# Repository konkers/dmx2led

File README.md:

# dmx2led
DMX512 to Addressable RGB LED Converter

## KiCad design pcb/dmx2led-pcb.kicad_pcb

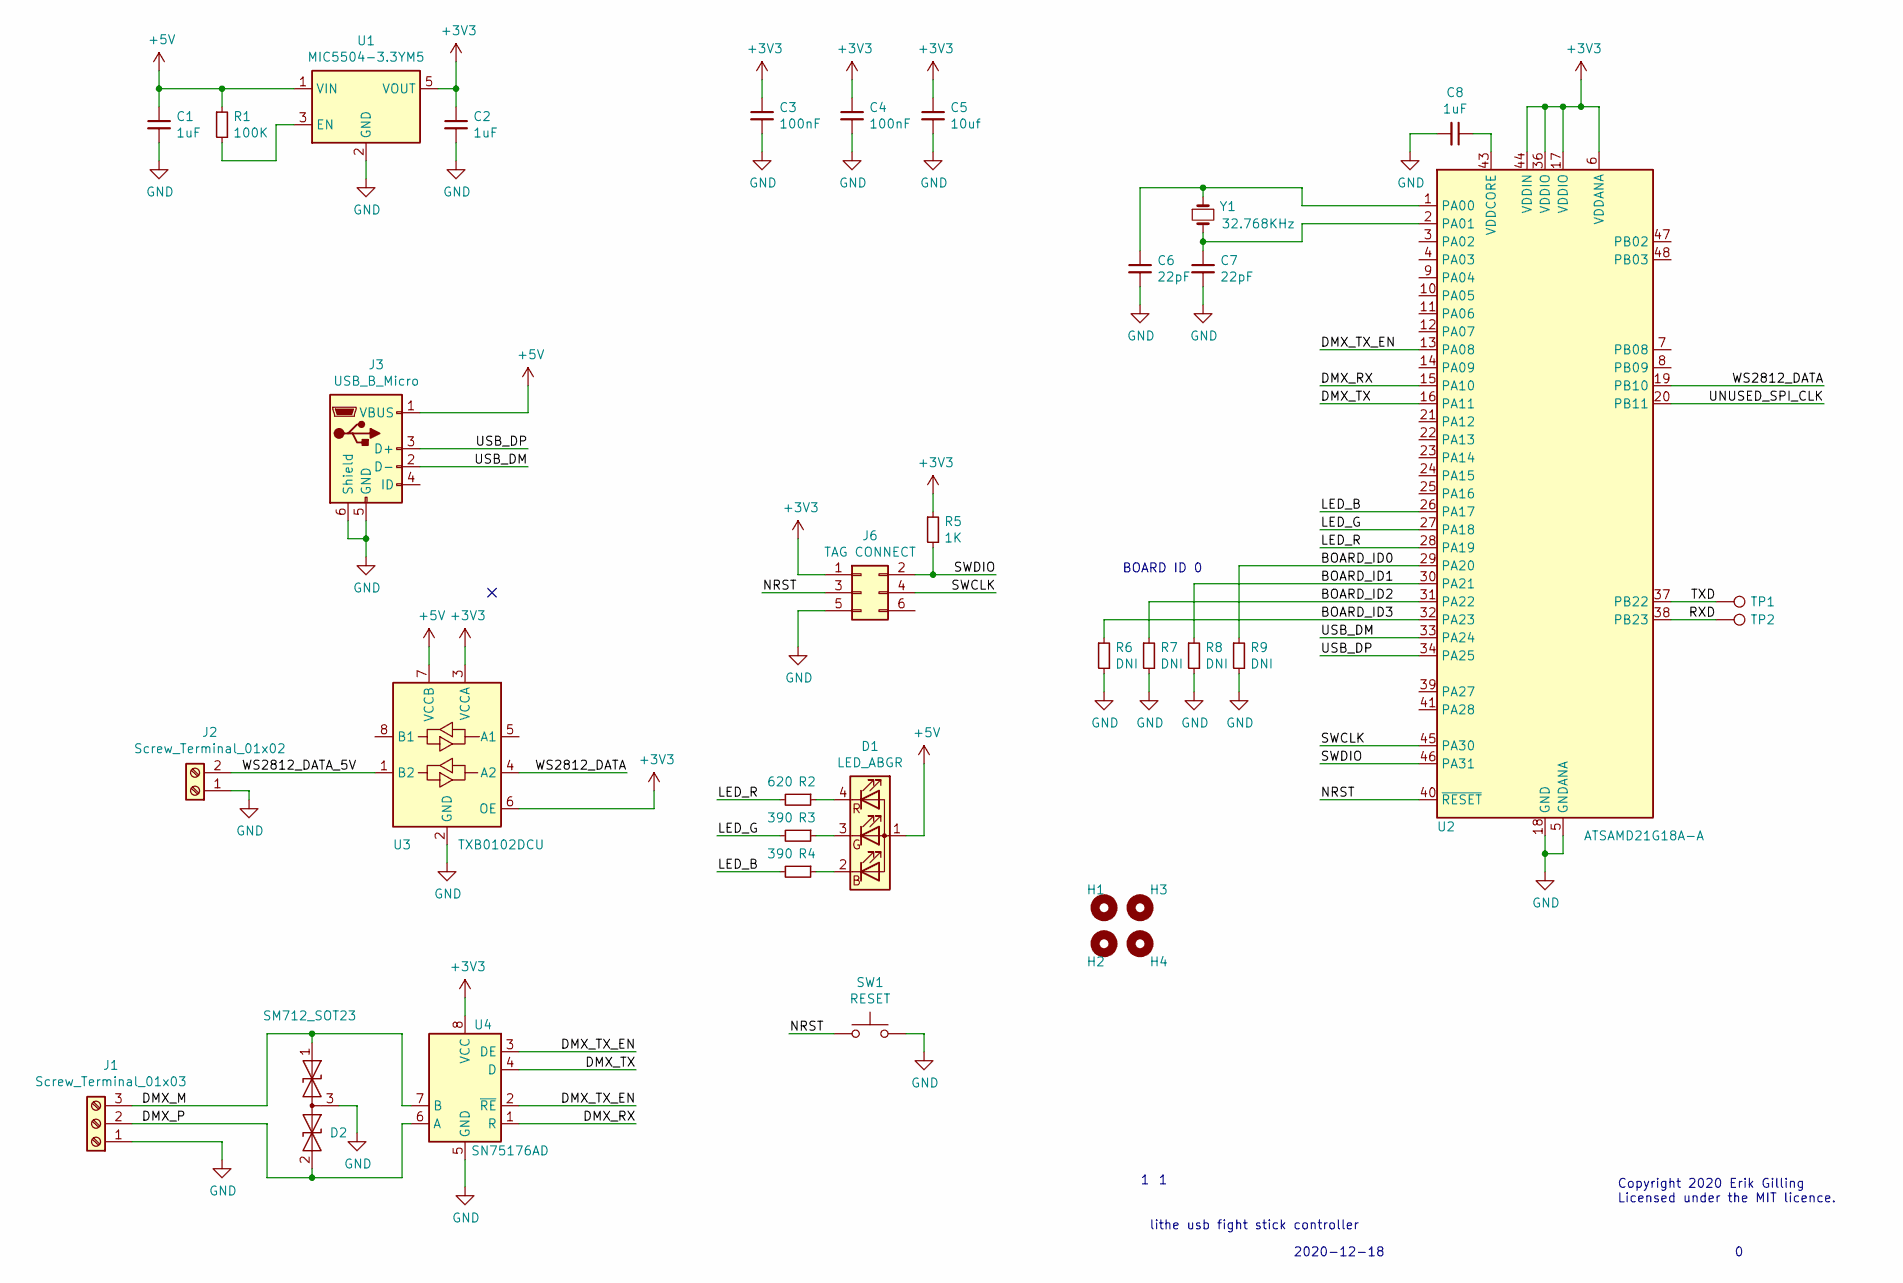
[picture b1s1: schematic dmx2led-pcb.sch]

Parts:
C1, C2, C8: 1uF; C_0402_1005Metric; DIGI_PN 1276-6524-2-ND
C3, C4: 100nF; C_0402_1005Metric; DIGI_PN 311-2077-1-ND
C5: 10uf; C_0603_1608Metric; DIGI_PN 490-3298-1-ND
C6, C7: 22pF; C_0402_1005Metric; DIGI_PN 445-1239-1-ND
D1: LED_ABGR; LED_Cree-PLCC4_2x2mm_CW; DIGI_PN CLMVC-FKA-CL1D1L71BB7C3C3TR-ND
D2: SM712_SOT23; SOT-23
H1, H2, H3, H4: MountingHole; MountingHole_3.2mm_M3_ISO7380
J1: Screw_Terminal_01x03; TerminalBlock_Phoenix_PT-1,5-3-3.5-H_1x03_P3.50mm_Horizontal
J2: Screw_Terminal_01x02; TerminalBlock_Phoenix_PT-1,5-2-3.5-H_1x02_P3.50mm_Horizontal
J3: USB_B_Micro; USB_Micro-B_Molex-105017-0001
J6: TAG CONNECT; Tag-Connect_TC2030-IDC-NL_2x03_P1.27mm_Vertical
R1: 100K; R_0402_1005Metric; DIGI_PN YAG2307TR-ND
R2: 620; R_0402_1005Metric; DIGI_PN 311-620LRTR-ND
R3, R4: 390; R_0402_1005Metric; DIGI_PN 311-390LRTR-ND
R5: 1K; R_0402_1005Metric; DIGI_PN 311-1.00KLRTR-ND
R6, R7, R8, R9: DNI; R_0402_1005Metric; DIGI_PN 311-0.0JRTR-ND
SW1: RESET; SW_SPST_EVQPE1; DIGI_PN CKN12311-2-ND
TP1, TP2: TestPoint; TestPoint_Pad_D1.0mm
U1: MIC5504-3.3YM5; SOT-23-5; DIGI_PN MIC5504-3.3YM5-T5TR-ND
U2: ATSAMD21G18A-A; TQFP-48_7x7mm_P0.5mm; DIGI_PN ATSAMD21G18A-AU-ND
U3: TXB0102DCU; VSSOP-8_2.4x2.1mm_P0.5mm
U4: SN75176AD; SOIC-8_3.9x4.9mm_P1.27mm
Y1: 32.768KHz; Crystal_SMD_MicroCrystal_CC7V-T1A-2Pin_3.2x1.5mm_HandSolder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; DIGI_PN 2195-CM7VT1ALOWESR32.768KHZ12.5PF20TAQC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

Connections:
+3V3: C2.1, C3.1, C4.1, C5.1, J6.1, R5.1, U1.5 (VOUT), U2.6 (VDDANA), U2.17 (VDDIO), U2.36 (VDDIO), U2.44 (VDDIN), U3.3 (VCCA), U3.6 (OE), U4.8 (VCC)
+5V: C1.1, D1.1 (A), J3.1 (VBUS), R1.1, U1.1 (VIN), U3.7 (VCCB)
/BOARD_ID0: R9.1, U2.29 (PA20)
/BOARD_ID1: R8.1, U2.30 (PA21)
/BOARD_ID2: R7.1, U2.31 (PA22)
/BOARD_ID3: R6.1, U2.32 (PA23)
/DMX_M: D2.1 (A1), J1.3, U4.7 (B)
/DMX_P: D2.2 (A2), J1.2, U4.6 (A)
/DMX_RX: U2.15 (PA10), U4.1 (R)
/DMX_TX: U2.16 (PA11), U4.4 (D)
/DMX_TX_EN: U2.13 (PA08), U4.2 (~RE), U4.3 (DE)
/LED_B: R4.2, U2.26 (PA17)
/LED_G: R3.2, U2.27 (PA18)
/LED_R: R2.2, U2.28 (PA19)
/NRST: J6.3, SW1.1, U2.40 (~RESET)
/RXD: TP2.1, U2.38 (PB23)
/SWCLK: J6.4, U2.45 (PA30)
/SWDIO: J6.2, R5.2, U2.46 (PA31)
/TXD: TP1.1, U2.37 (PB22)
/UNUSED_SPI_CLK: U2.20 (PB11)
/USB_DM: J3.2 (D-), U2.33 (PA24)
/USB_DP: J3.3 (D+), U2.34 (PA25)
/WS2812_DATA: U2.19 (PB10), U3.4 (A2)
/WS2812_DATA_5V: J2.2, U3.1 (B2)
GND: C1.2, C2.2, C3.2, C4.2, C5.2, C6.2, C7.2, C8.2, D2.3 (common), J1.1, J2.1, J3.5 (GND), J3.6 (Shield), J6.5, R6.2, R7.2, R8.2, R9.2, SW1.2, U1.2 (GND), U2.5 (GNDANA), U2.18 (GND), U2.35 (GND), U2.42 (GND), U3.2 (GND), U4.5 (GND)
unnamed: C6.1, U2.1 (PA00), Y1.1
unnamed: C7.1, U2.2 (PA01), Y1.2
unnamed: C8.1, U2.43 (VDDCORE)
unnamed: D1.2 (BK), R4.1
unnamed: D1.3 (GK), R3.1
unnamed: D1.4 (RK), R2.1
unnamed: R1.2, U1.3 (EN)

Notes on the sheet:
lithe usb fight stick controller
2020-12-18
Copyright 2020 Erik Gilling Licensed under the MIT licence.
BOARD ID 0

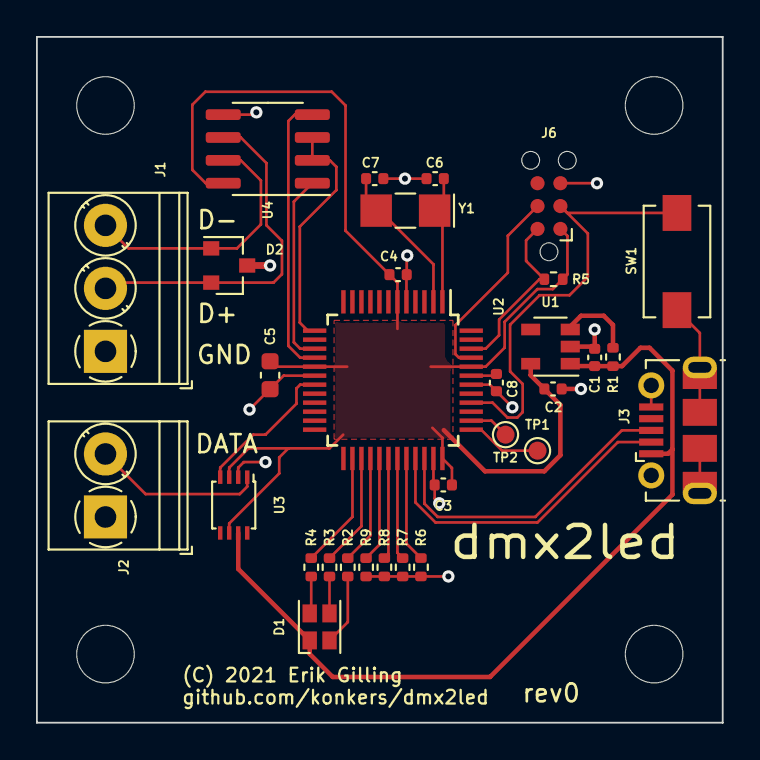
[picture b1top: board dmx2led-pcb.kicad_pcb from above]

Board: 2 copper layers, 38.1 x 38.1 mm, 35 parts (0 on the bottom side), 31 nets.

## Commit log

2021-08-25 prototype working
2021-08-25 cleanup
2021-08-25 more dep pruning
2021-08-26 Initial prototype firmware.
    DMX to WS2812b functional
2021-08-26 rev0 PCB

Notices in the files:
pcb/dmx2led-pcb.kicad_pcb:
(C) 2021 Erik Gilling
